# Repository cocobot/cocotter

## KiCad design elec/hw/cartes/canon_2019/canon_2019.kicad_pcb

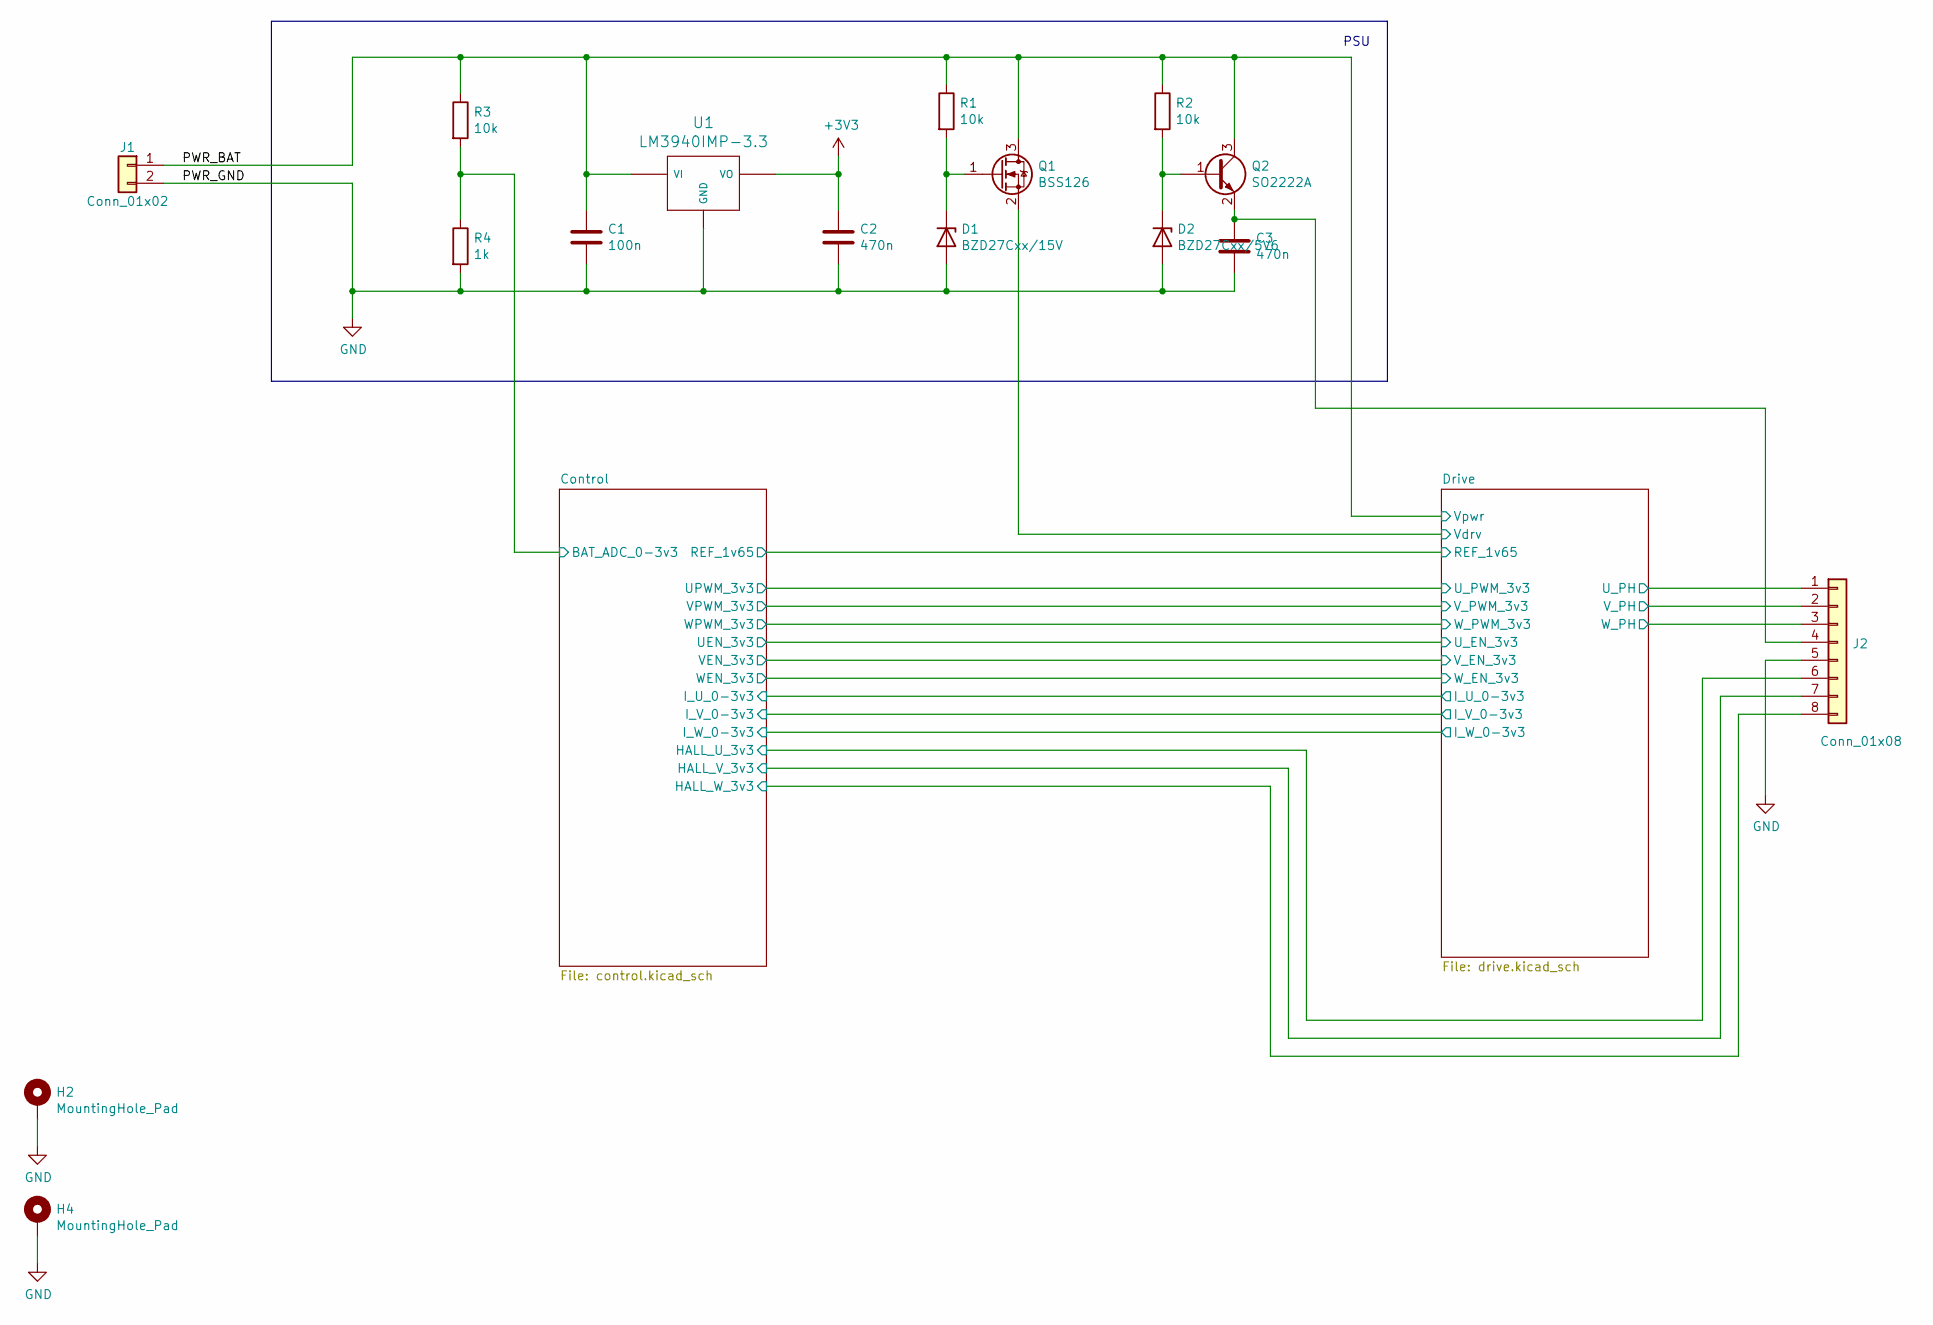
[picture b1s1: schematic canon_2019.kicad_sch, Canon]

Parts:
C1: 100n; C_0603
C2, C3: 470n; C_0603
D1: BZD27Cxx/15V; D_SOD-323
D2: BZD27Cxx/5V6; D_SOD-323
H2, H4: MountingHole_Pad; MountingHole_3.2mm_M3
J1: Conn_01x02; Pin_Header_Straight_1x02_Pitch2.54mm
J2: Conn_01x08; Pin_Header_Straight_1x08_Pitch2.54mm
Q1: BSS126; SOT-23
Q2: SO2222A; SOT-23
R1, R2, R3: 10k; R_0603
R4: 1k; R_0603
U1: LM3940IMP-3.3; SOT-223-3_TabPin2

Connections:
+3V3: C2.1, U1.3 (VO); also elsewhere on the board
/Control/BAT_ADC_0-3v3: R3.2, R4.1; also elsewhere on the board
/Control/HALL_U_3v3: J2.6; also elsewhere on the board
/Control/HALL_V_3v3: J2.7; also elsewhere on the board
/Control/HALL_W_3v3: J2.8; also elsewhere on the board
/Drive/U_PH: J2.1; also elsewhere on the board
/Drive/V_PH: J2.2; also elsewhere on the board
/Drive/Vdrv: Q1.2 (S); also elsewhere on the board
/Drive/W_PH: J2.3; also elsewhere on the board
/PWR_BAT: C1.1, J1.1, Q1.3 (D), Q2.3 (C), R1.1, R2.1, R3.1, U1.1 (VI); also elsewhere on the board
GND: C1.2, C2.2, C3.2, D1.2 (A), D2.2 (A), H2.1, H4.1, J1.2, J2.5, R4.2, U1.2 (GND); also elsewhere on the board
unnamed: C3.1, J2.4, Q2.2 (E)
unnamed: D1.1 (K), Q1.1 (G), R1.2
unnamed: D2.1 (K), Q2.1 (B), R2.2

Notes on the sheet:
PSU

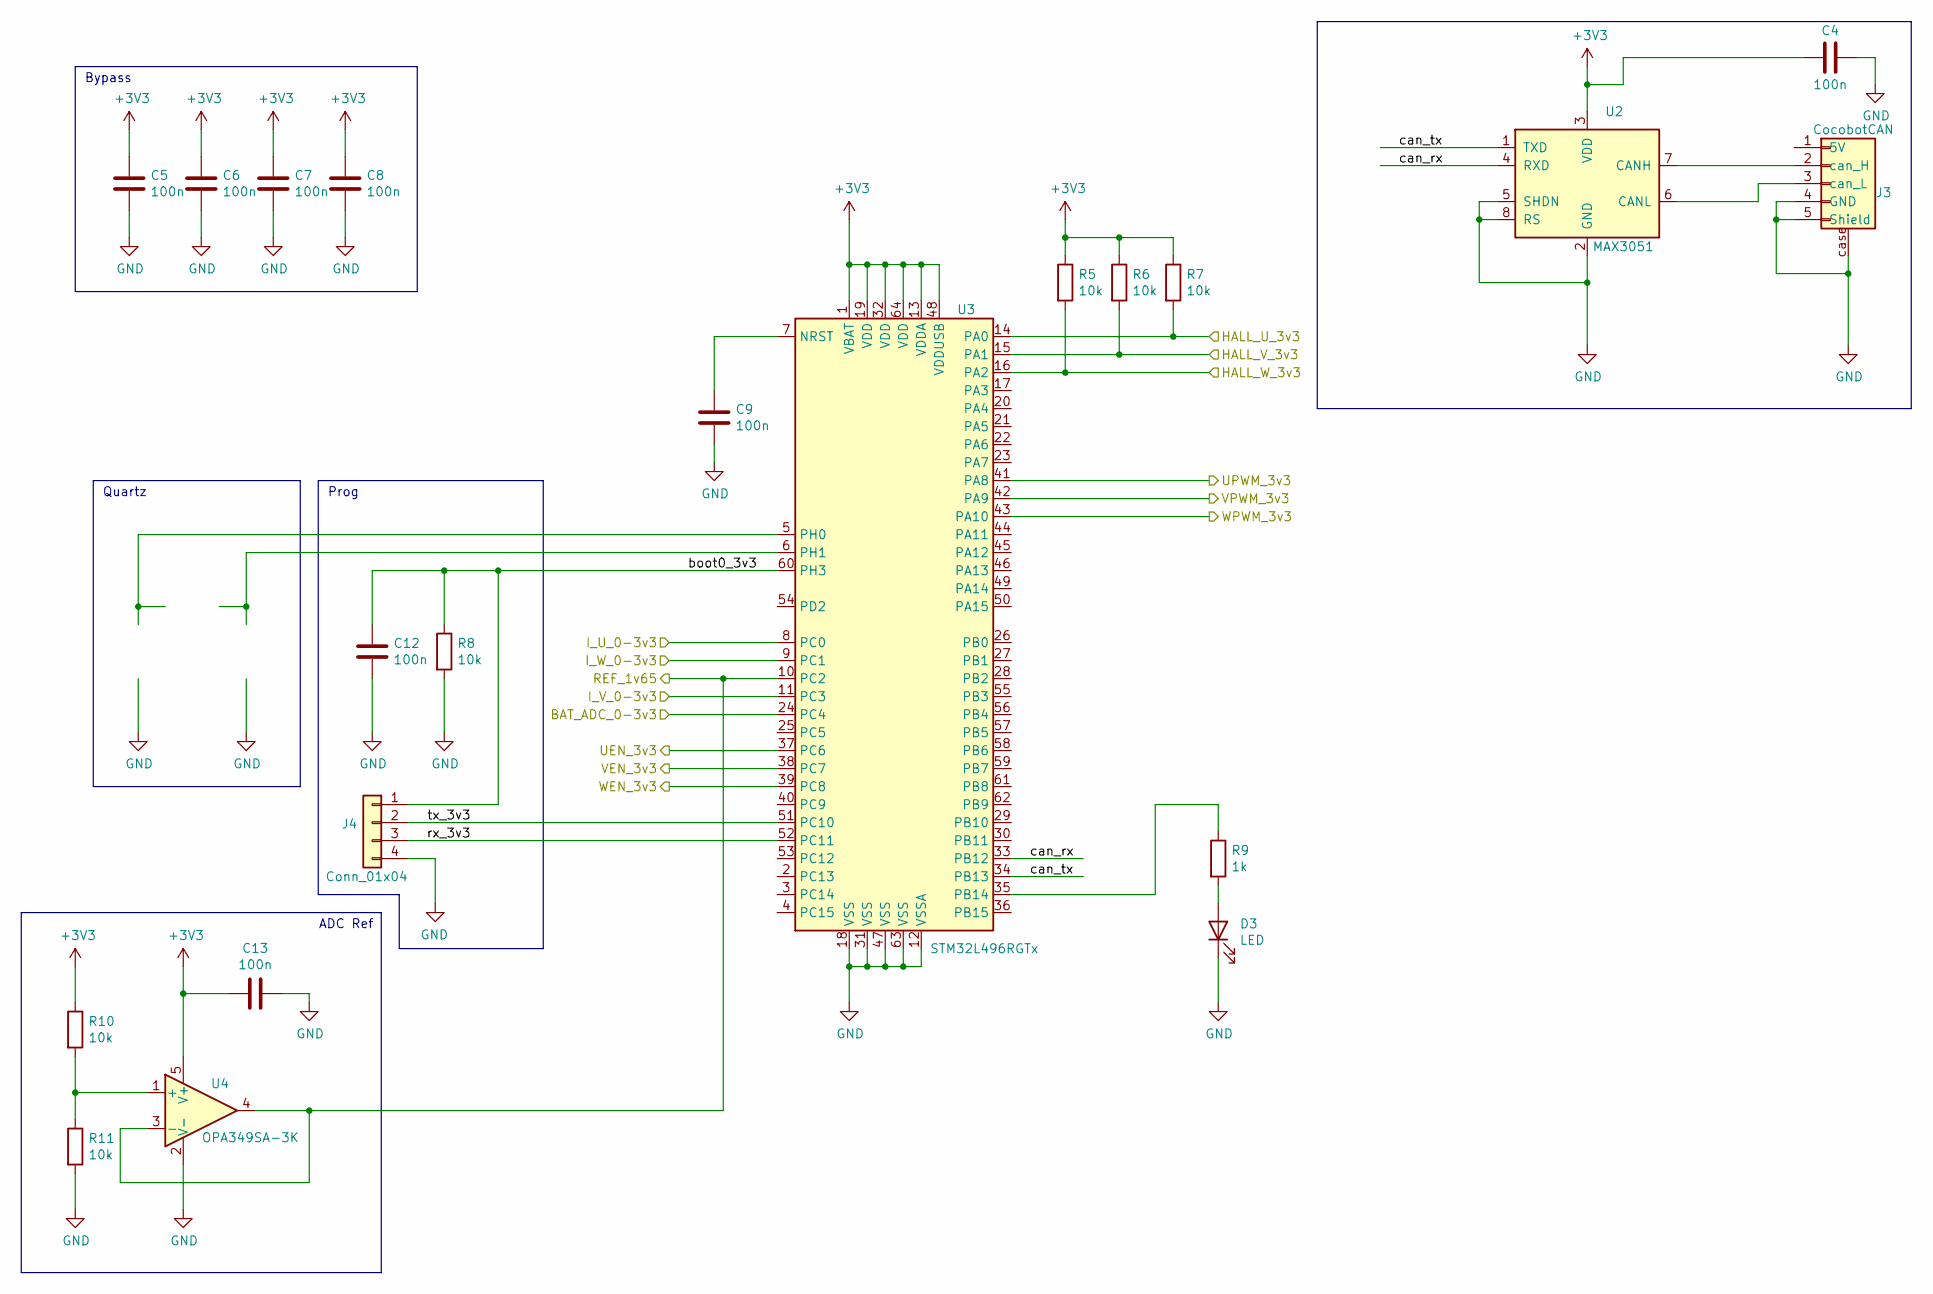
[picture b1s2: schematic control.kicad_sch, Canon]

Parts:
C4, C5, C6, C7, C8, C9, C12, C13: 100n; C_0603
D3: LED; LED_0805
J3: CocobotCAN; JST_PH_S5B-PH-SM4-TB_05x2.00mm_Angled
J4: Conn_01x04; Pin_Header_Straight_1x04_Pitch2.54mm
R5, R6, R7, R8, R10, R11: 10k; R_0603
R9: 1k; R_0603
U2: MAX3051; SOIC-8_3.9x4.9mm_Pitch1.27mm
U3: STM32L496RGTx; LQFP-64_10x10mm_Pitch0.5mm
U4: OPA349SA-3K; SOT-353_SC-70-5

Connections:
+3V3: C4.1, C5.1, C6.1, C7.1, C8.1, C13.2, R5.1, R6.1, R7.1, R10.1, U2.3 (VDD), U3.1 (VBAT), U3.13 (VDDA), U3.19 (VDD), U3.32 (VDD), U3.48 (VDDUSB), U3.64 (VDD), U4.5 (V+); also elsewhere on the board
/Control/BAT_ADC_0-3v3: U3.24 (PC4); also elsewhere on the board
/Control/HALL_U_3v3: R7.2, U3.14 (PA0); also elsewhere on the board
/Control/HALL_V_3v3: R6.2, U3.15 (PA1); also elsewhere on the board
/Control/HALL_W_3v3: R5.2, U3.16 (PA2); also elsewhere on the board
/Control/I_U_0-3v3: U3.8 (PC0); also elsewhere on the board
/Control/I_V_0-3v3: U3.11 (PC3); also elsewhere on the board
/Control/I_W_0-3v3: U3.9 (PC1); also elsewhere on the board
/Control/REF_1v65: U3.10 (PC2), U4.3 (-), U4.4; also elsewhere on the board
/Control/UEN_3v3: U3.37 (PC6); also elsewhere on the board
/Control/UPWM_3v3: U3.41 (PA8); also elsewhere on the board
/Control/VEN_3v3: U3.38 (PC7); also elsewhere on the board
/Control/VPWM_3v3: U3.42 (PA9); also elsewhere on the board
/Control/WEN_3v3: U3.39 (PC8); also elsewhere on the board
/Control/WPWM_3v3: U3.43 (PA10); also elsewhere on the board
/Control/boot0_3v3: C12.1, J4.1, R8.1, U3.60 (PH3)
/Control/can_rx: U2.4 (RXD), U3.33 (PB12)
/Control/can_tx: U2.1 (TXD), U3.34 (PB13)
/Control/rx_3v3: J4.3, U3.52 (PC11)
/Control/tx_3v3: J4.2, U3.51 (PC10)
GND: C4.2, C5.2, C6.2, C7.2, C8.2, C9.2, C12.2, C13.1, D3.1 (K), J3.4 (GND), J3.5 (Shield), J3.case, J4.4, R8.2, R11.2, U2.2 (GND), U2.5 (SHDN), U2.8 (RS), U3.12 (VSSA), U3.18 (VSS), U3.31 (VSS), U3.47 (VSS), U3.63 (VSS), U4.2 (V-); also elsewhere on the board
unnamed: C9.1, U3.7 (NRST)
unnamed: D3.2 (A), R9.2
unnamed: J3.2 (can_H), U2.7 (CANH)
unnamed: J3.3 (can_L), U2.6 (CANL)
unnamed: R9.1, U3.35 (PB14)
unnamed: R10.2, R11.1, U4.1 (+)

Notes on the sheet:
ADC Ref
Prog
Quartz
Bypass

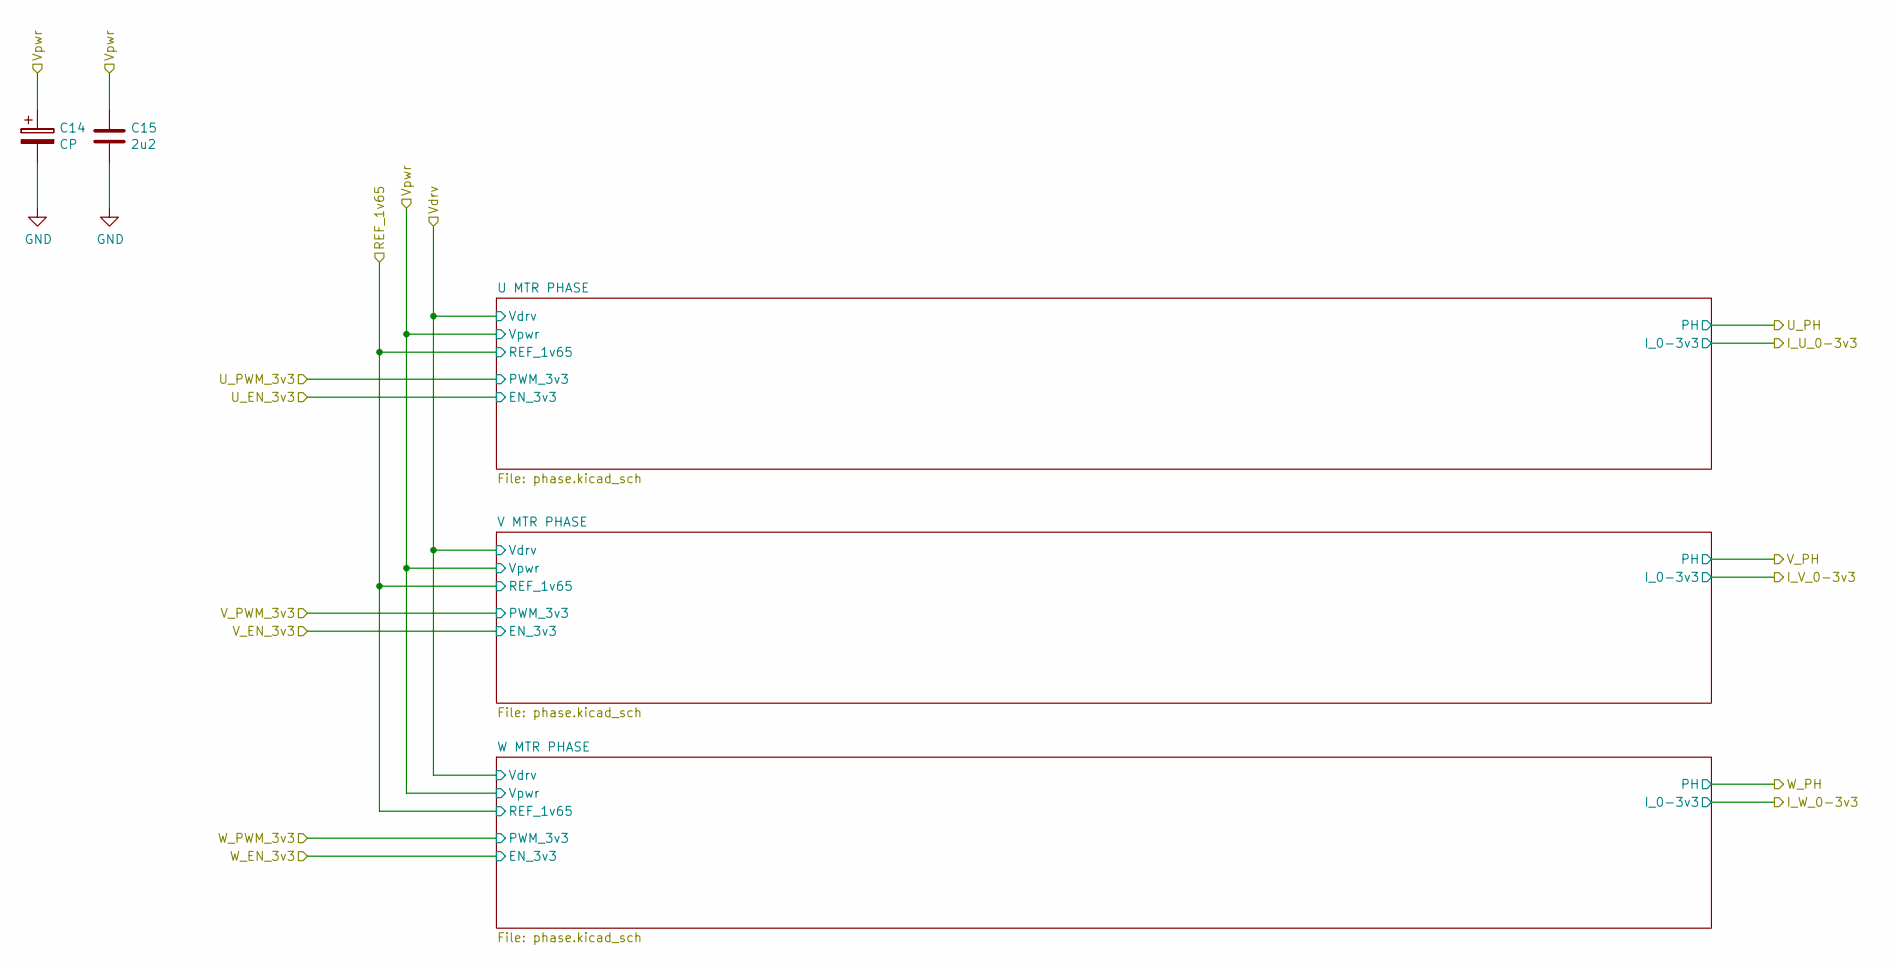
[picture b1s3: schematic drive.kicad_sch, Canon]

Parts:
C14: CP; c_elec_6.3x7.7
C15: 2u2; C_0603

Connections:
/PWR_BAT: C14.1, C15.1; also elsewhere on the board
GND: C14.2, C15.2; also elsewhere on the board

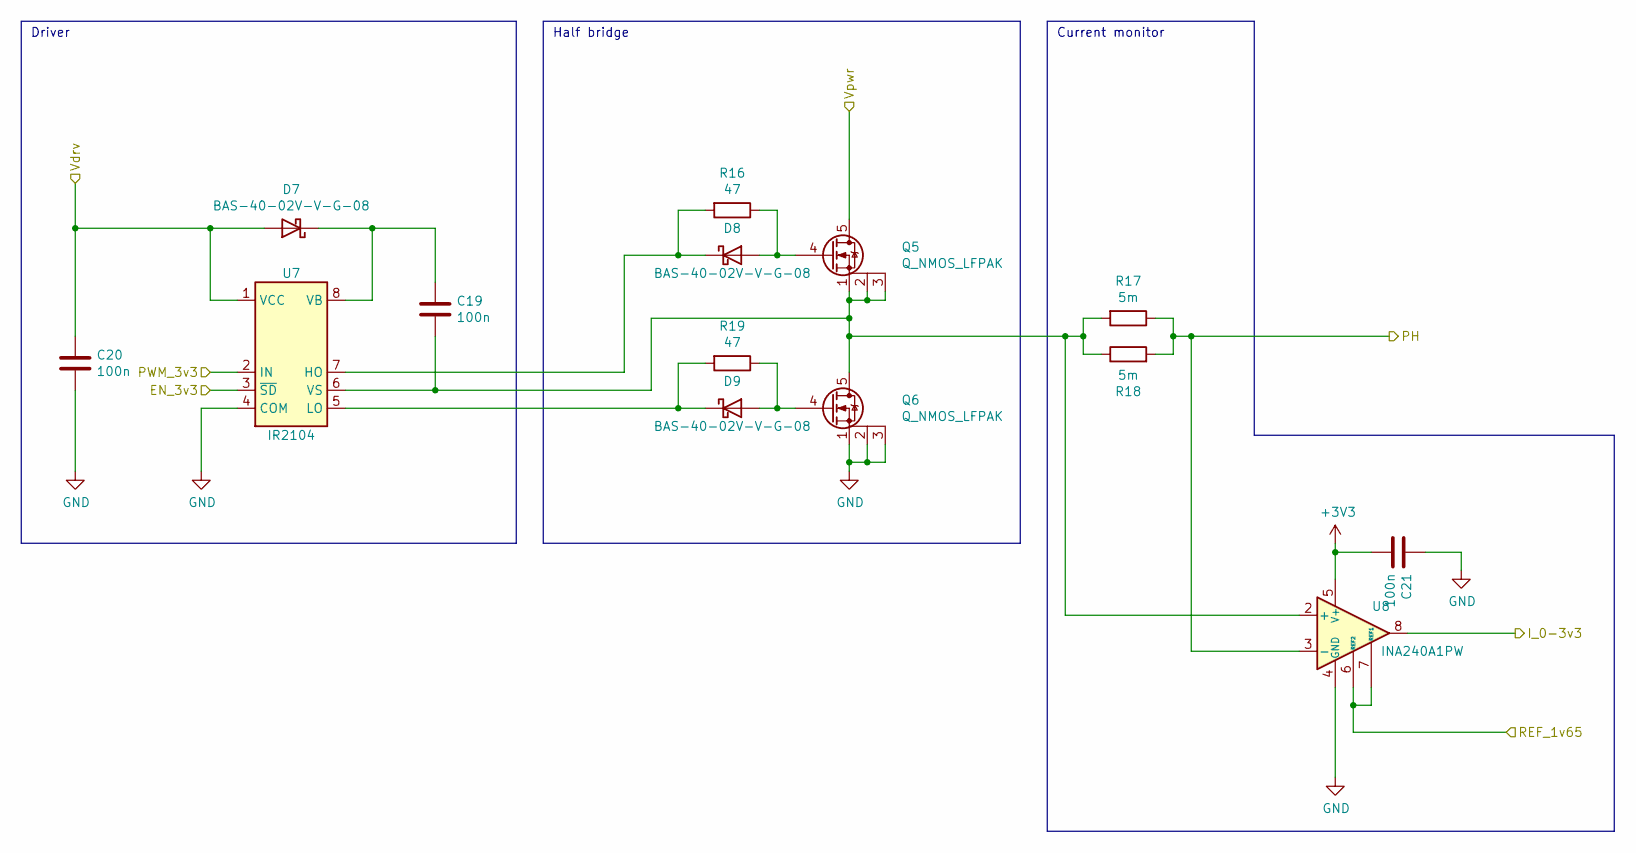
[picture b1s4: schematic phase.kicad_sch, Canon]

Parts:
C19, C20, C21: 100n; C_0603
D7, D8, D9: BAS-40-02V-V-G-08; D_SOD-523
Q5, Q6: Q_NMOS_LFPAK; SOT-669_LFPAK
R16, R19: 47; R_0603
R17, R18: 5m; R_1206
U7: IR2104; SOIC-8_3.9x4.9mm_Pitch1.27mm
U8: INA240A1PW; TSSOP-8_4.4x3mm_Pitch0.65mm

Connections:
+3V3: C21.2, U8.5 (V+); also elsewhere on the board
/Control/I_V_0-3v3: U8.8; also elsewhere on the board
/Control/REF_1v65: U8.6 (REF2), U8.7 (REF1); also elsewhere on the board
/Control/VEN_3v3: U7.3 (~SD); also elsewhere on the board
/Control/VPWM_3v3: U7.2 (IN); also elsewhere on the board
/Drive/V_PH: R17.1, R18.2, U8.3 (-); also elsewhere on the board
/Drive/Vdrv: C20.1, D7.2 (A), U7.1 (VCC); also elsewhere on the board
/PWR_BAT: Q5.5 (D); also elsewhere on the board
GND: C20.2, C21.1, Q6.1 (S), Q6.2 (D), Q6.3 (D), U7.4 (COM), U8.1 (GND), U8.4 (GND); also elsewhere on the board
unnamed: C19.1, D7.1 (K), U7.8 (VB)
unnamed: C19.2, Q5.1 (S), Q5.2 (D), Q5.3 (D), Q6.5 (D), R17.2, R18.1, U7.6 (VS), U8.2 (+)
unnamed: D8.1 (K), R16.2, U7.7 (HO)
unnamed: D8.2 (A), Q5.4 (G), R16.1
unnamed: D9.1 (K), R19.2, U7.5 (LO)
unnamed: D9.2 (A), Q6.4 (G), R19.1

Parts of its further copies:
C16, C17, C18, C22, C23, C24: 100n; C_0603
D4, D5, D6, D10, D11, D12: BAS-40-02V-V-G-08; D_SOD-523
Q3, Q4, Q7, Q8: Q_NMOS_LFPAK; SOT-669_LFPAK
R12, R15, R20, R23: 47; R_0603
R13, R14, R21, R22: 5m; R_1206
U5, U9: IR2104; SOIC-8_3.9x4.9mm_Pitch1.27mm
U6, U10: INA240A1PW; TSSOP-8_4.4x3mm_Pitch0.65mm

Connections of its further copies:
+3V3: C18.2, C24.2, U6.5 (V+), U10.5 (V+); also elsewhere on the board
/Control/I_U_0-3v3: U6.8; also elsewhere on the board
/Control/I_W_0-3v3: U10.8; also elsewhere on the board
/Control/REF_1v65: U6.6 (REF2), U6.7 (REF1), U10.6 (REF2), U10.7 (REF1); also elsewhere on the board
/Control/UEN_3v3: U5.3 (~SD); also elsewhere on the board
/Control/UPWM_3v3: U5.2 (IN); also elsewhere on the board
/Control/WEN_3v3: U9.3 (~SD); also elsewhere on the board
/Control/WPWM_3v3: U9.2 (IN); also elsewhere on the board
/Drive/U_PH: R13.1, R14.2, U6.3 (-); also elsewhere on the board
/Drive/Vdrv: C17.1, C23.1, D4.2 (A), D10.2 (A), U5.1 (VCC), U9.1 (VCC); also elsewhere on the board
/Drive/W_PH: R21.1, R22.2, U10.3 (-); also elsewhere on the board
/PWR_BAT: Q3.5 (D), Q7.5 (D); also elsewhere on the board
GND: C17.2, C18.1, C23.2, C24.1, Q4.1 (S), Q4.2 (D), Q4.3 (D), Q8.1 (S), Q8.2 (D), Q8.3 (D), U5.4 (COM), U6.1 (GND), U6.4 (GND), U9.4 (COM), U10.1 (GND), U10.4 (GND); also elsewhere on the board
unnamed: C16.1, D4.1 (K), U5.8 (VB)
unnamed: C16.2, Q3.1 (S), Q3.2 (D), Q3.3 (D), Q4.5 (D), R13.2, R14.1, U5.6 (VS), U6.2 (+)
unnamed: C22.1, D10.1 (K), U9.8 (VB)
unnamed: C22.2, Q7.1 (S), Q7.2 (D), Q7.3 (D), Q8.5 (D), R21.2, R22.1, U9.6 (VS), U10.2 (+)
unnamed: D5.1 (K), R12.2, U5.7 (HO)
unnamed: D5.2 (A), Q3.4 (G), R12.1
unnamed: D6.1 (K), R15.2, U5.5 (LO)
unnamed: D6.2 (A), Q4.4 (G), R15.1
unnamed: D11.1 (K), R20.2, U9.7 (HO)
unnamed: D11.2 (A), Q7.4 (G), R20.1
unnamed: D12.1 (K), R23.2, U9.5 (LO)
unnamed: D12.2 (A), Q8.4 (G), R23.1

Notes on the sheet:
Half bridge
Current monitor
Driver

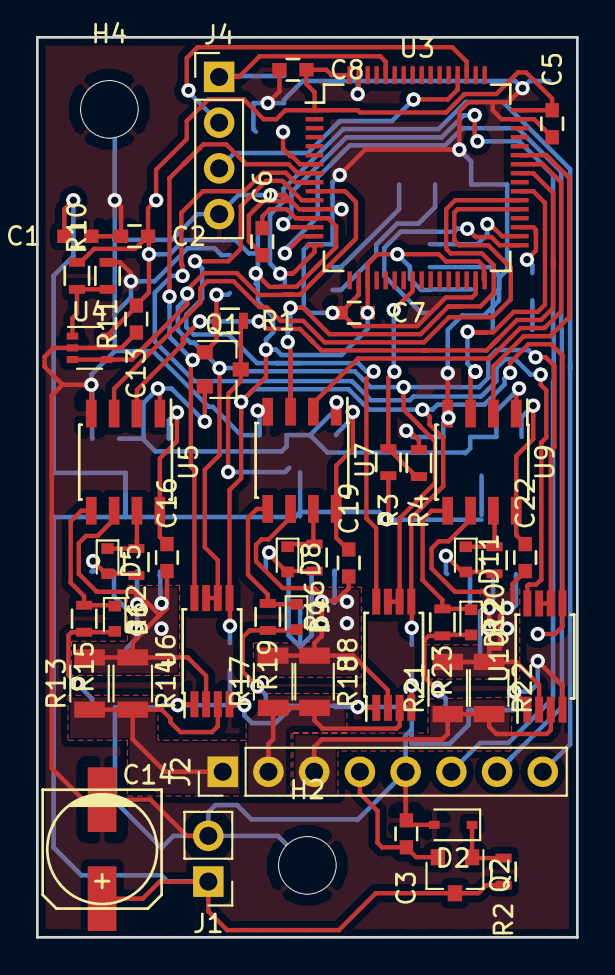
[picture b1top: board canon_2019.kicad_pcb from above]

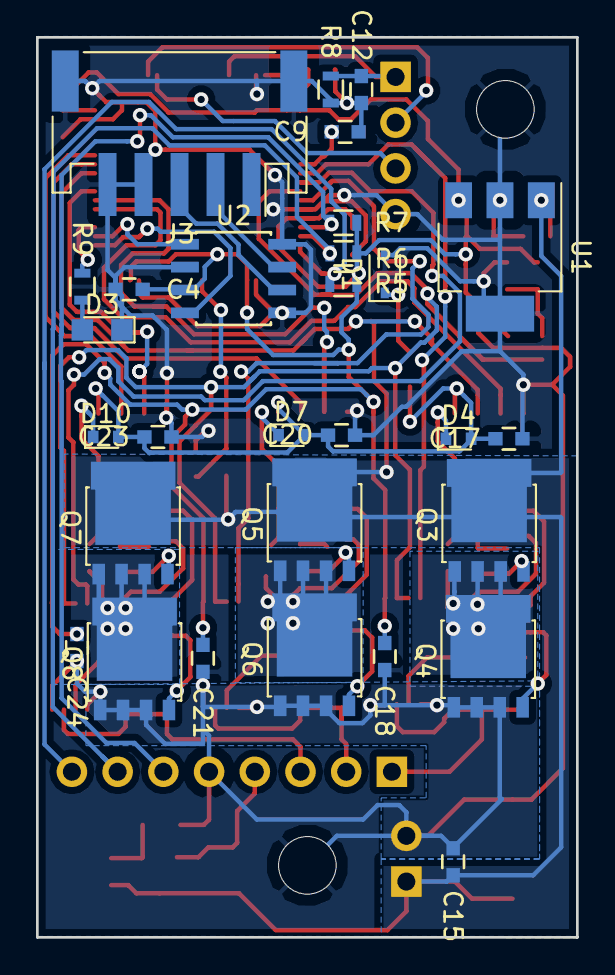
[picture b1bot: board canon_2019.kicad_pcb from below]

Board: 2 copper layers, 30.0 x 50.0 mm, 81 parts (29 on the bottom side), 53 nets.

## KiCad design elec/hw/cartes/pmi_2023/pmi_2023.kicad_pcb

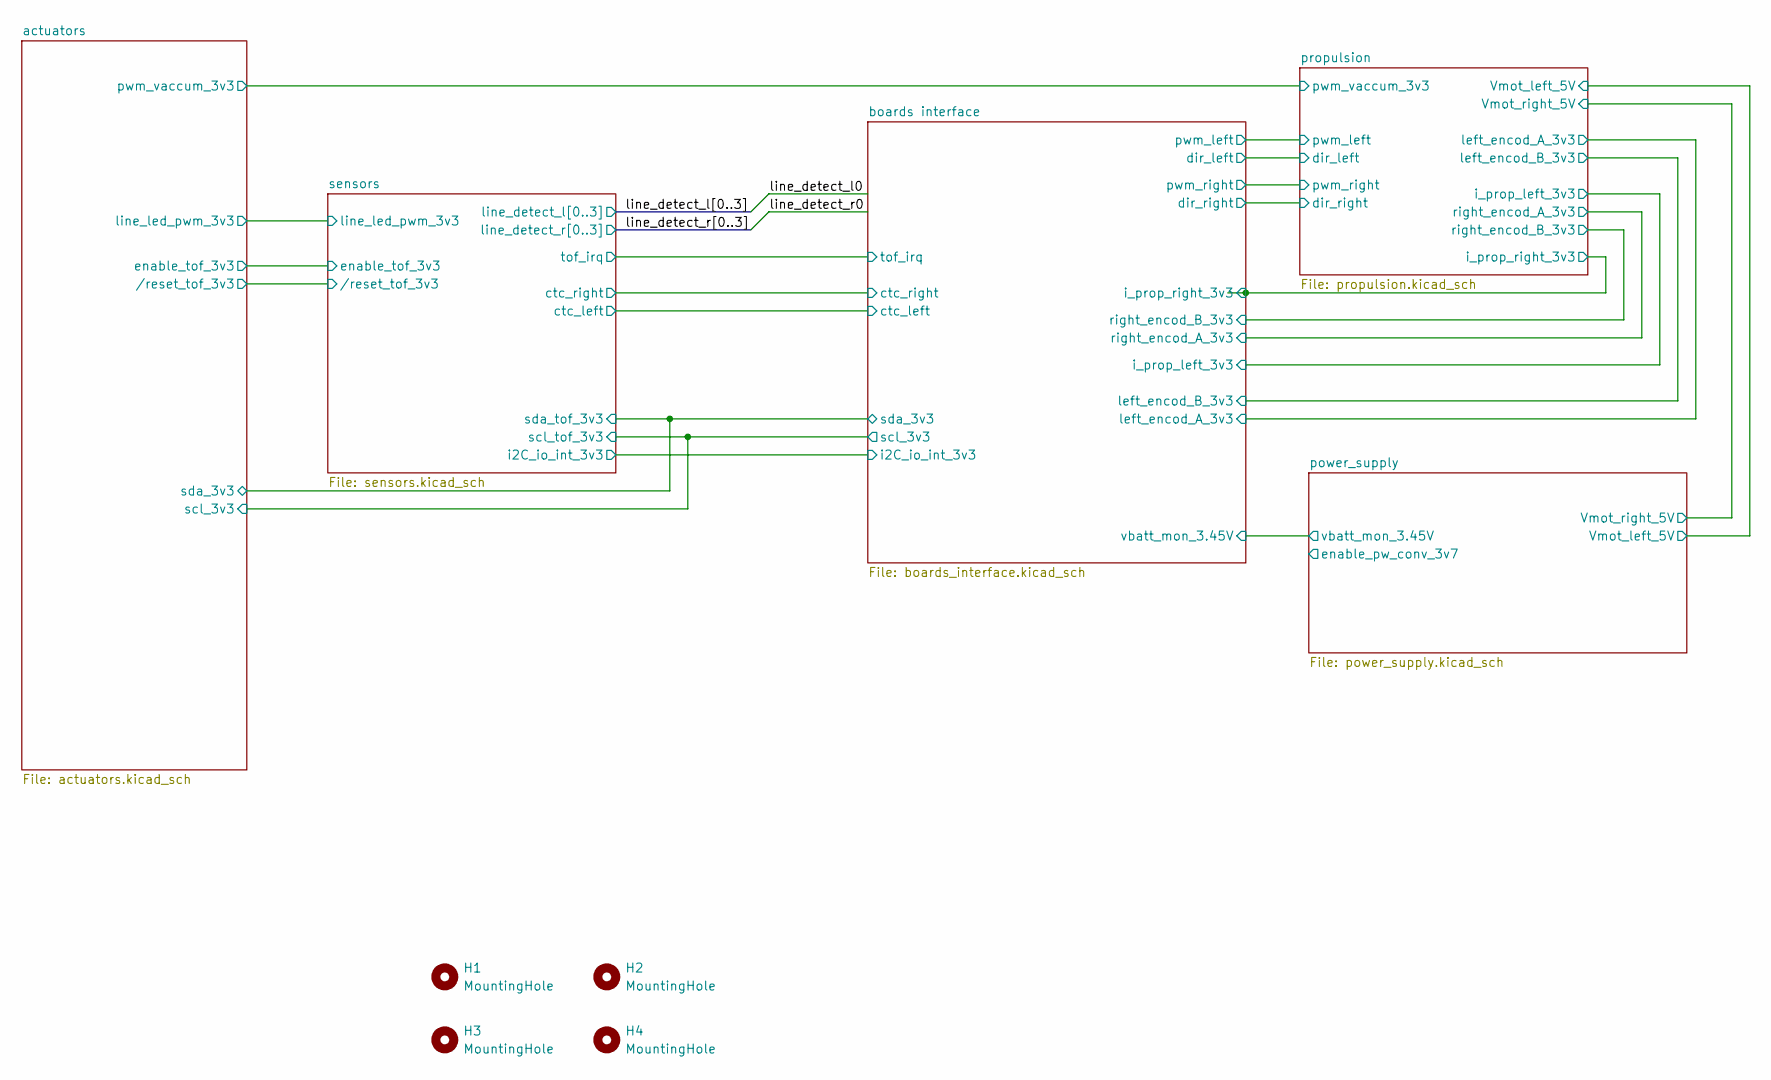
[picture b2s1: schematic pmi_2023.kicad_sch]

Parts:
H1, H2, H3, H4: MountingHole; MountingHole_2.1mm

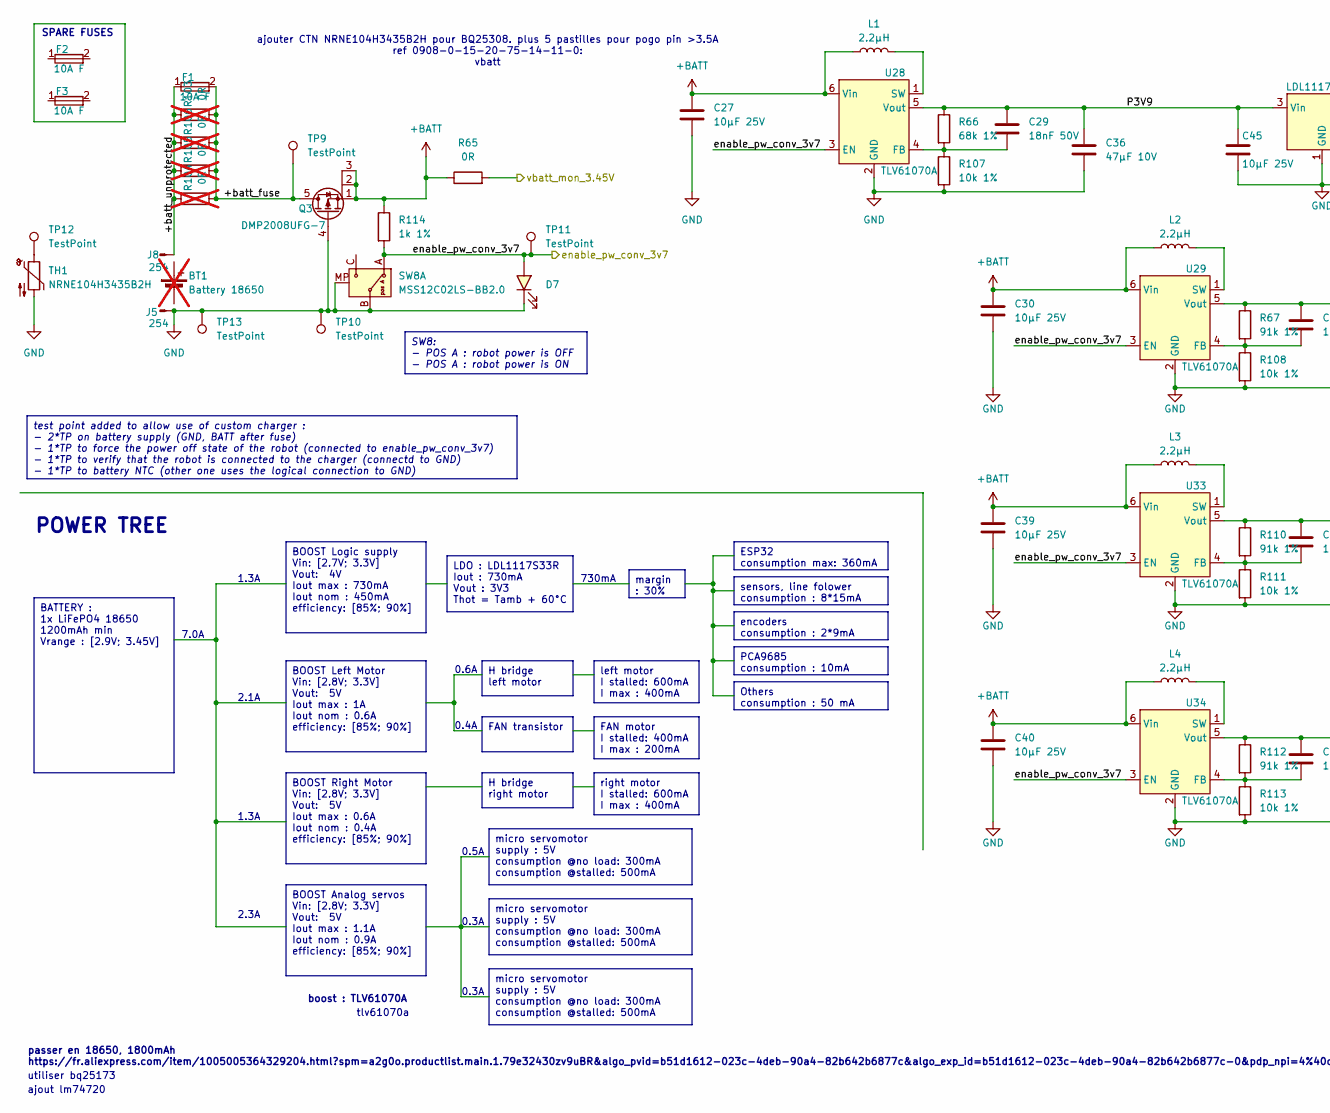
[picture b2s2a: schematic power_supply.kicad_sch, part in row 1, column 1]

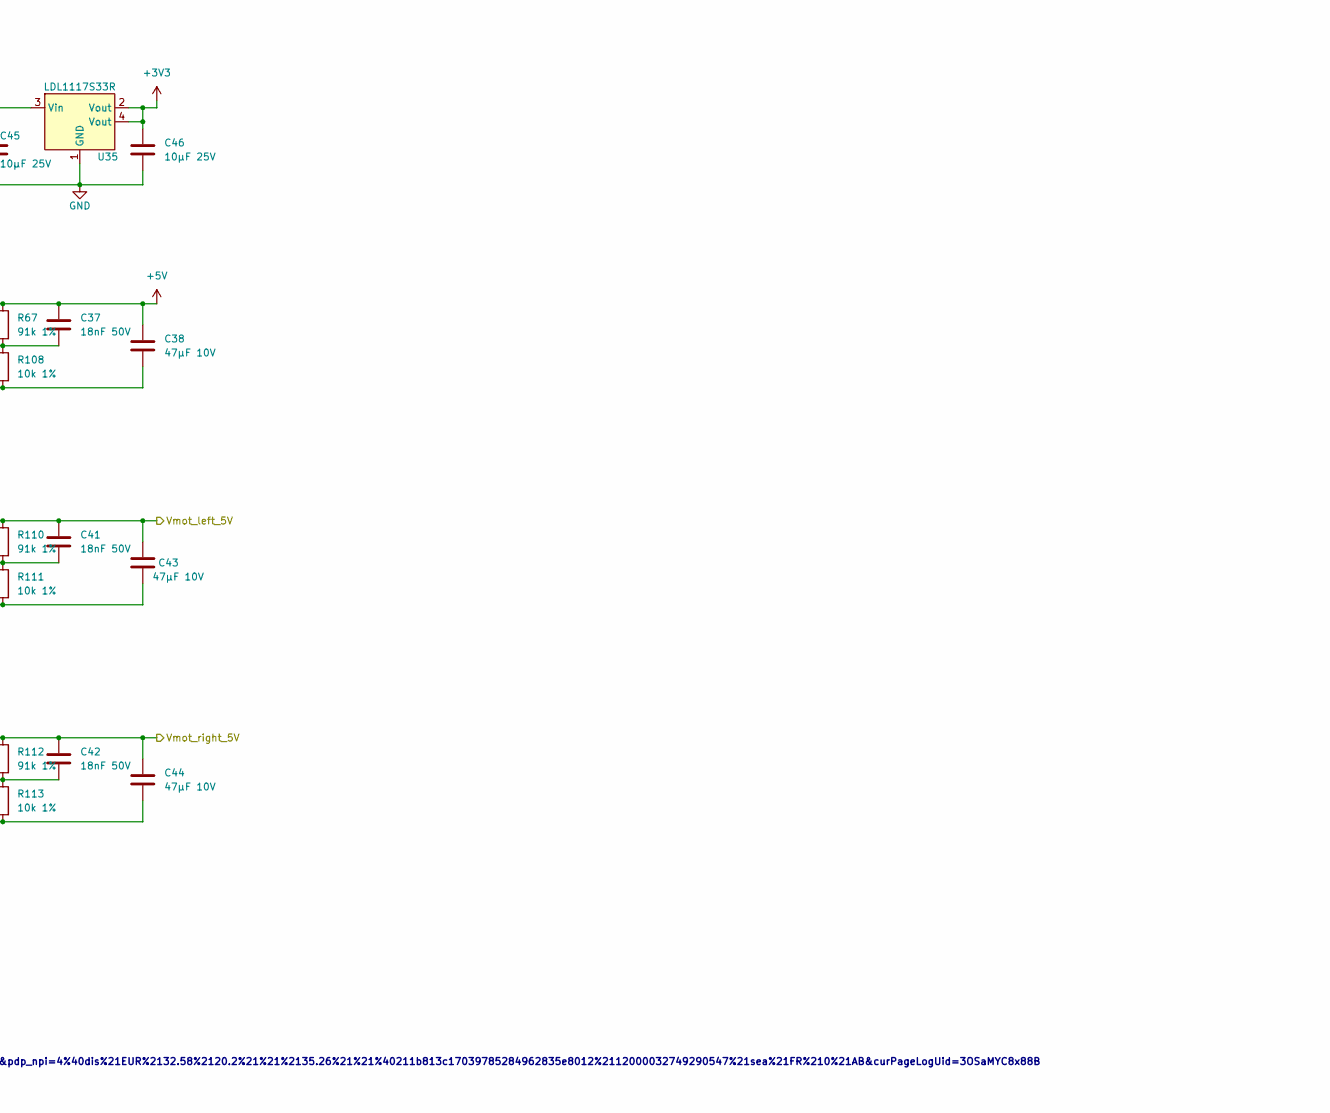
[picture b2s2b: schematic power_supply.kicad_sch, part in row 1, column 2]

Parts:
BT1: Battery 18650; not fitted
C27, C30, C39, C40, C45, C46: 10µF 25V; C_0805_2012Metric; JLCPCB Part # C15850
C29, C37, C41, C42: 18nF 50V; C_0603_1608Metric; JLCPCB Part # C107079
C36, C38, C43, C44: 47µF 10V; C_1206_3216Metric; JLCPCB Part # C96123
D7: green, 0603; LED_0603_1608Metric; DIGIKEY_REF 3147-B19Y1UYG-20C000313U1930CT-ND
F1, F2, F3: 10A F; JFC2410; JLCPCB Part # C136374
J5, J8: 254; JLCPCB Part # C2979182
L1, L2, L3, L4: 2.2µH; L_Kyocera_07A7_7.3x6.6mm; MOUSER 581-LMLP07A7M2R2DTAS
Q3: DMP2008UFG-7; Diodes_PowerDI3333-8; JLCPCB Part # C461052
R65: 0R; r0603_reflow; JLCPCB Part # C431718
R66: 68k 1%; r0603_reflow; JLCPCB Part # C23231
R67, R110, R112: 91k 1%; r0603_reflow; JLCPCB Part # C23265
R103, R104, R105, R106: 0R; r0603_reflow; JLCPCB Part # C431718; not fitted
R107, R108, R111, R113: 10k 1%; r0603_reflow; mouser 603-RC0603FR-10100KL
R114: 1k 1%; r0603_reflow; mouser 603-RC0603FR-10100KL
SW8: MSS12C02LS-BB2.0; JLCPCB Part # C3008585
TH1: NRNE104H3435B2H; CTN-NRN
TP9, TP10, TP11, TP12, TP13: TestPoint; testpoint-THT-0.5mm
U28, U29, U33, U34: TLV61070A; SOT-23-6
U35: LDL1117S33R; SOT-223

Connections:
+3V3: C46.1, U35.2 (Vout), U35.4 (Vout); also elsewhere on the board
+5V: C37.1, C38.1, R67.1, U29.5 (Vout); also elsewhere on the board
+BATT: C27.1, C30.1, C39.1, C40.1, L1.1, L2.1, L3.1, L4.1, Q3.1 (S), Q3.2 (S), Q3.3 (S), R65.1, R114.1, U28.6 (Vin), U29.6 (Vin), U33.6 (Vin), U34.6 (Vin)
/boards interface/vbatt_mon_3.45V: R65.2; also elsewhere on the board
/power_supply/+batt_fuse: F1.2, Q3.5 (D), R103.2, R104.2, R105.2, R106.2, TP9.1
/power_supply/+batt_unprotected: F1.1, J8.1 (GND), R103.1, R104.1, R105.1, R106.1
/power_supply/P3V9: C29.1, C36.1, C45.1, R66.1, U28.5 (Vout), U35.3 (Vin)
/power_supply/Vmot_left_5V: C41.1, C43.1, R110.1, U33.5 (Vout); also elsewhere on the board
/power_supply/Vmot_right_5V: C42.1, C44.1, R112.1, U34.5 (Vout); also elsewhere on the board
/power_supply/enable_pw_conv_3v7: D7.A, R114.2, SW8.A, TP11.1, U28.3 (EN), U29.3 (EN), U33.3 (EN), U34.3 (EN)
GND: C27.2, C30.2, C36.2, C38.2, C39.2, C40.2, C43.2, C44.2, C45.2, C46.2, D7.C, J5.1 (GND), Q3.4 (G), R107.2, R108.2, R111.2, R113.2, SW8.B, SW8.MP, TH1.2, TP10.1, TP13.1, U28.2 (GND), U29.2 (GND), U33.2 (GND), U34.2 (GND), U35.1 (GND); also elsewhere on the board
unnamed: TH1.1, TP12.1
unnamed: C29.2, R66.2, R107.1, U28.4 (FB)
unnamed: L1.2, U28.1 (SW)
unnamed: C37.2, R67.2, R108.1, U29.4 (FB)
unnamed: L2.2, U29.1 (SW)
unnamed: C41.2, R110.2, R111.1, U33.4 (FB)
unnamed: L3.2, U33.1 (SW)
unnamed: C42.2, R112.2, R113.1, U34.4 (FB)
unnamed: L4.2, U34.1 (SW)

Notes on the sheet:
FAN motor I stalled: 400mA I max : 200mA
H bridge left motor
micro servomotor supply : 5V consumption @no load: 300mA consumption @stalled: 500mA
right motor I stalled: 600mA I max : 400mA
BATTERY : 1x LiFePO4 18650 1200mAh min Vrange : [2.9V; 3.45V]
encoders consumption : 2*9mA
BOOST Right Motor Vin: [2.8V; 3.3V] Vout: 5V Iout max : 0.6A Iout nom : 0.4A efficiency: [85%; 90%]
FAN transistor
left motor I stalled: 600mA I max : 400mA
ESP32 consumption max: 360mA
H bridge right motor
Others consumption : 50 mA
BOOST Left Motor Vin: [2.8V; 3.3V] Vout: 5V Iout max : 1A Iout nom : 0.6A efficiency: [85%; 90%]
BOOST Logic supply Vin: [2.7V; 3.3V] Vout: 4V Iout max : 730mA Iout nom : 450mA efficiency: [85%; 90%]
PCA9685 consumption : 10mA
SW8: - POS A : robot power is OFF - POS A : robot power is ON
test point added to allow use of custom charger : - 2*TP on battery supply (GND, BATT after fuse) - 1*TP to force the power off state of the robot (connected to enable_pw_conv_3v7) - 1*TP to verify that the robot is connected to the charger (connectd to GND) - 1*TP to battery NTC (other one uses th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
margin : 30%
BOOST Analog servos Vin: [2.8V; 3.3V] Vout: 5V Iout max : 1.1A Iout nom : 0.9A efficiency: [85%; 90%]
LDO : LDL1117S33R Iout : 730mA Vout : 3V3 Thot = Tamb + 60°C
sensors, line folower consumption : 8*15mA
ajouter CTN NRNE104H3435B2H pour BQ25308. plus 5 pastilles pour pogo pin >3.5A ref 0908-0-15-20-75-14-11-0: vbatt
0.3A
1.3A
ajout lm74720
POWER TREE
passer en 18650, 1800mAh https://fr.aliexpress.com/item/1005005364329204.html?spm=a2g0o.productlist.main.1.79e32430zv9uBR&algo_pvid=b51d1612-023c-4deb-90a4-82b642b6877c&algo_exp_id=b51d1612-023c-4deb-90a4-82b642b6877c-0&pdp_npi=4%40dis%21EUR%2132.58%2120.2%21%21%2135.26%21%21%40211b813c170397852849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
0.4A
2.1A
tlv61070a
utiliser bq25173
0.6A
2.3A
boost : TLV61070A
SPARE FUSES
7.0A
0.5A
730mA

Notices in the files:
elec/hw/cartes/canon_2019/canon_2019.kicad_sch:
CC-BY 4.0
